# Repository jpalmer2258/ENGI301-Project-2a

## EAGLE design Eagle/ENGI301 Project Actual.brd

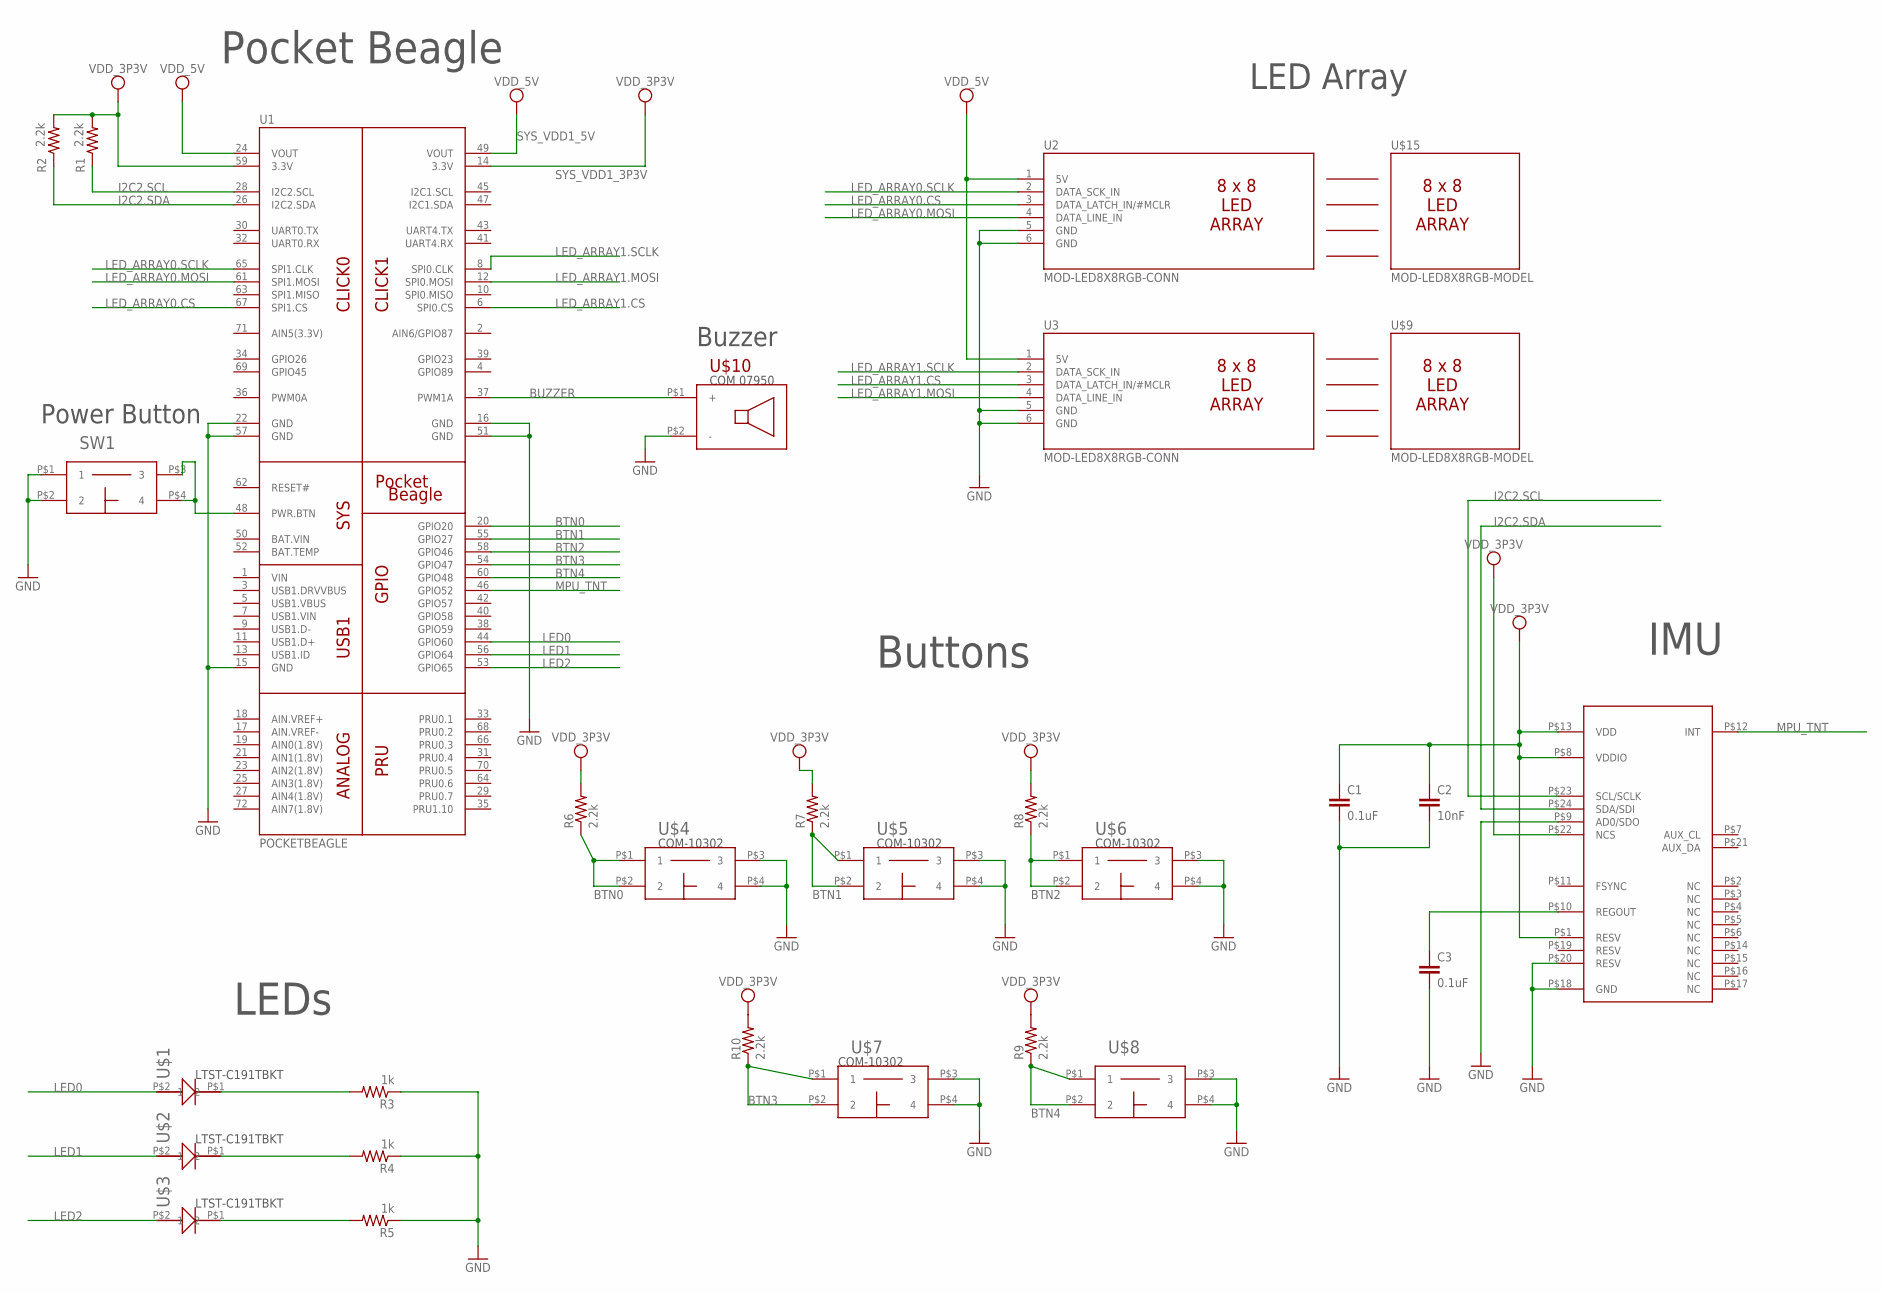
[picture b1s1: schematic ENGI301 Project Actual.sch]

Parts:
C1, C3: 0.1uF; C0603
C2: 10nF; C0603
R1, R2, R6, R7, R8, R9, R10: 2.2k; R0603
R3, R4, R5: 1k; R0603
SW1: BUTTON
U1: POCKETBEAGLE
U2, U3: MOD-LED8X8RGB-CONN; FE06W
U6: MPU-9250; QFN3
U$1, U$2, U$3: LED
U$4, U$5, U$6, U$7, U$8: BUTTON
U$10: BUZZER

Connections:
BTN0: R6.1, U1.20 (GPIO20), U$4.P$1 (1), U$4.P$2 (2)
BTN1: R7.1, U1.55 (GPIO27), U$5.P$1 (1), U$5.P$2 (2)
BTN2: R8.1, U1.58 (GPIO46), U$6.P$1 (1), U$6.P$2 (2)
BTN3: R10.1, U1.54 (GPIO47), U$7.P$1 (1), U$7.P$2 (2)
BTN4: R9.1, U1.60 (GPIO48), U$8.P$1 (1), U$8.P$2 (2)
BUZZER: U1.37 (PWM1A), U$10.P$1 (+)
GND: C1.2, C2.2, C3.2, R3.1, R4.1, R5.1, SW1.P$1 (1), SW1.P$2 (2), U1.15 (GND), U1.16 (GND), U1.22 (GND), U1.51 (GND), U1.57 (GND), U2.5 (GND), U2.6 (GND), U3.5 (GND), U3.6 (GND), U6.P$9 (AD0/SDO), U6.P$18 (GND), U6.P$20 (RESV), U$4.P$3 (3), U$4.P$4 (4), U$5.P$3 (3), U$5.P$4 (4), U$6.P$3 (3), U$6.P$4 (4), U$7.P$3 (3), U$7.P$4 (4), U$8.P$3 (3), U$8.P$4 (4), U$10.P$2 (-)
I2C2.SCL: R1.1, U1.28 (I2C2.SCL), U6.P$23 (SCL/SCLK)
I2C2.SDA: R2.1, U1.26 (I2C2.SDA), U6.P$24 (SDA/SDI)
LED0: U1.44 (GPIO60), U$1.P$2 (2)
LED1: U1.56 (GPIO64), U$2.P$2 (2)
LED2: U1.53 (GPIO65), U$3.P$2 (2)
LED_ARRAY0.CS: U1.67 (SPI1.CS), U2.3 (DATA_LATCH_IN/#MCLR)
LED_ARRAY0.MOSI: U1.61 (SPI1.MOSI), U2.4 (DATA_LINE_IN)
LED_ARRAY0.SCLK: U1.65 (SPI1.CLK), U2.2 (DATA_SCK_IN)
LED_ARRAY1.CS: U1.6 (SPI0.CS), U3.3 (DATA_LATCH_IN/#MCLR)
LED_ARRAY1.MOSI: U1.12 (SPI0.MOSI), U3.4 (DATA_LINE_IN)
LED_ARRAY1.SCLK: U1.8 (SPI0.CLK), U3.2 (DATA_SCK_IN)
MPU_TNT: U1.46 (GPIO52), U6.P$12 (INT)
unnamed: SW1.P$3 (3), SW1.P$4 (4), U1.48 (PWR.BTN)
unnamed: R3.2, U$1.P$1 (1)
unnamed: R4.2, U$2.P$1 (1)
unnamed: R5.2, U$3.P$1 (1)
unnamed: C3.1, U6.P$10 (REGOUT)
SYS_VDD1_3P3V: C1.1, C2.1, R1.2, R2.2, R6.2, R7.2, R8.2, R9.2, R10.2, U1.14 (3.3V), U1.59 (3.3V), U6.P$1 (RESV), U6.P$8 (VDDIO), U6.P$13 (VDD), U6.P$22 (NCS)

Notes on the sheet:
COM 07950
COM-10302
LTST-C191TBKT
Pocket Beagle
Power Button
Buzzer
Buttons
LEDs
IMU
LED Array

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
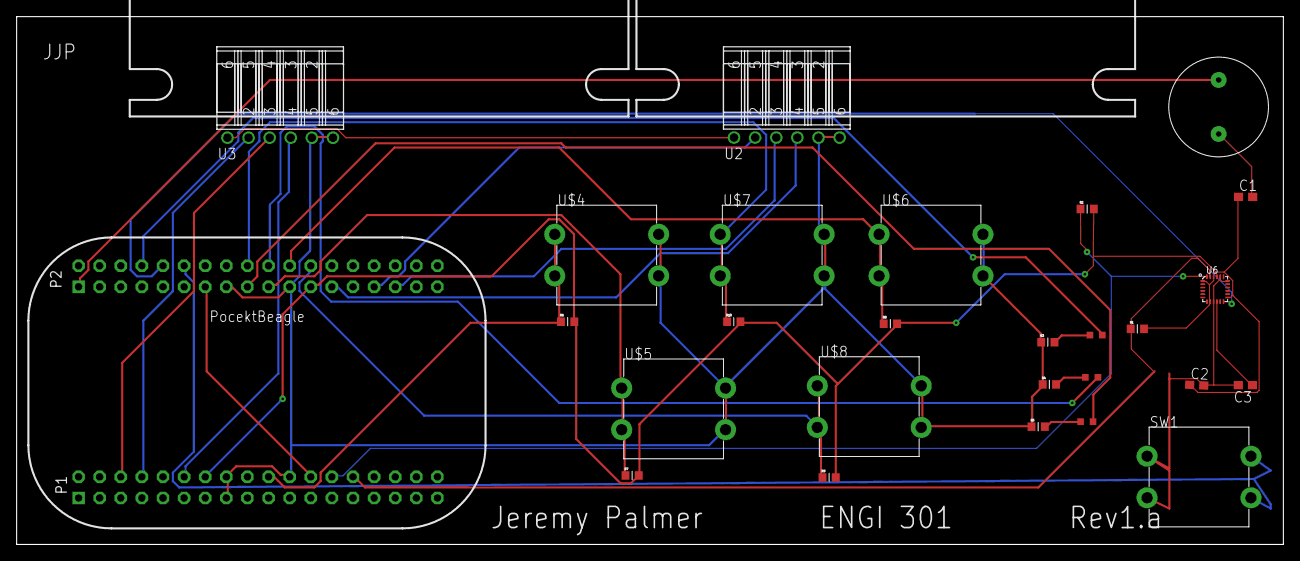
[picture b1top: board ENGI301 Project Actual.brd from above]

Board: 4 copper layers, 152.4 x 63.5 mm, 31 parts (0 on the bottom side), 27 nets.

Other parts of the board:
U$11, U$12, U$13, U$14: MOD-LED8X8RGB

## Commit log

2018-04-20 Final PCB Project 2a Palmer
2018-04-20 THIS IS THE REAL FINAL ONE - PALMER
    Sorry for this mess of a gitHub
